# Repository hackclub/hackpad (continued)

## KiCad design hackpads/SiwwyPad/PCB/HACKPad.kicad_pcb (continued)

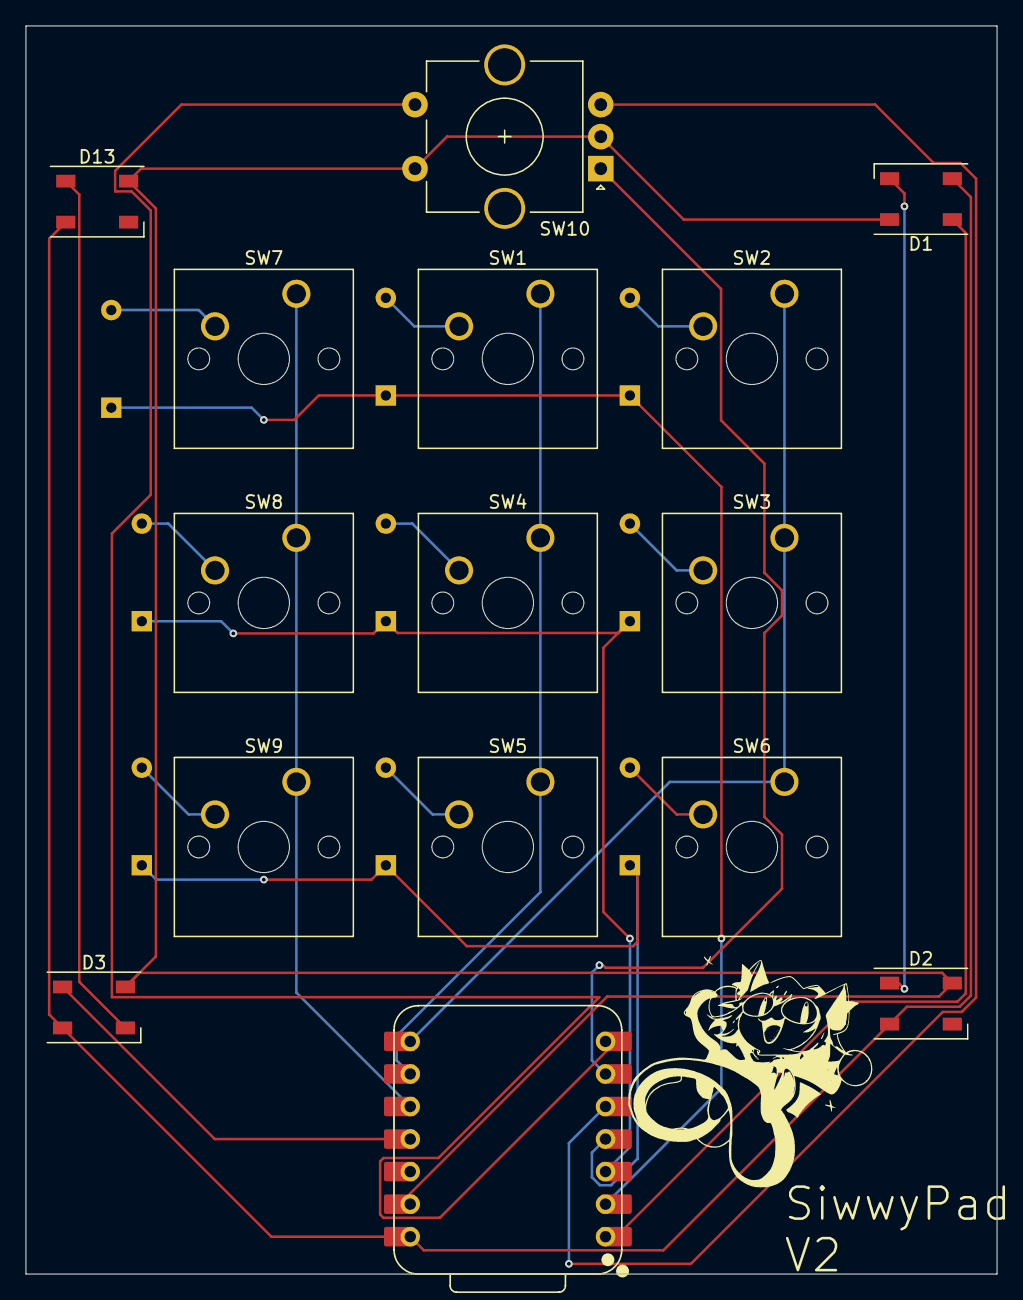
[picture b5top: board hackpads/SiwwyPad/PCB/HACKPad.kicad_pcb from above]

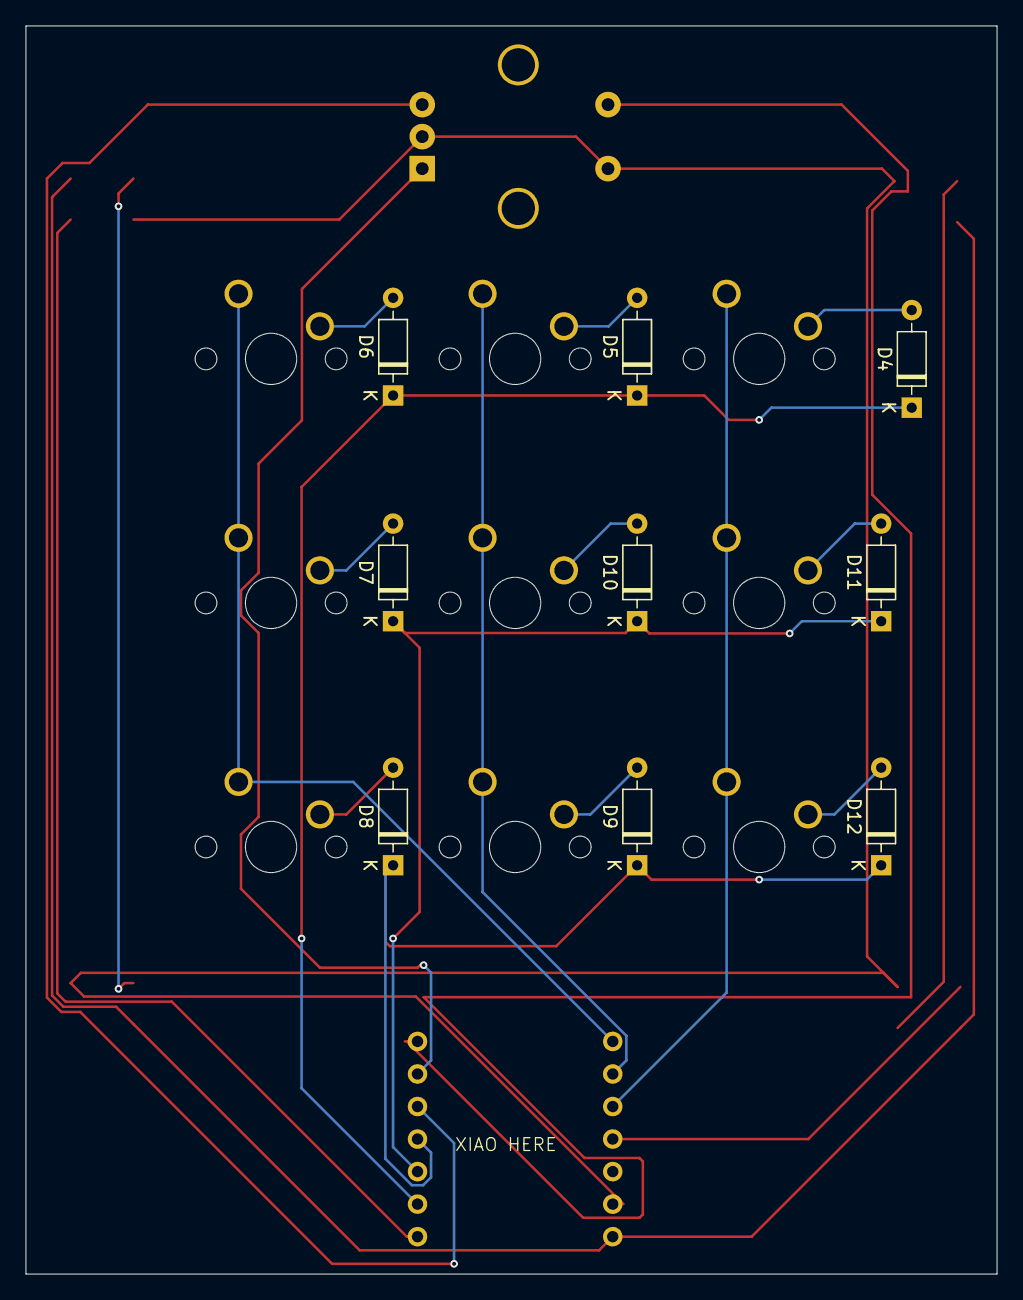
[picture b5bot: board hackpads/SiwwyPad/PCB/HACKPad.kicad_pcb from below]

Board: 2 copper layers, 75.8 x 97.4 mm, 24 parts (9 on the bottom side), 24 nets.
